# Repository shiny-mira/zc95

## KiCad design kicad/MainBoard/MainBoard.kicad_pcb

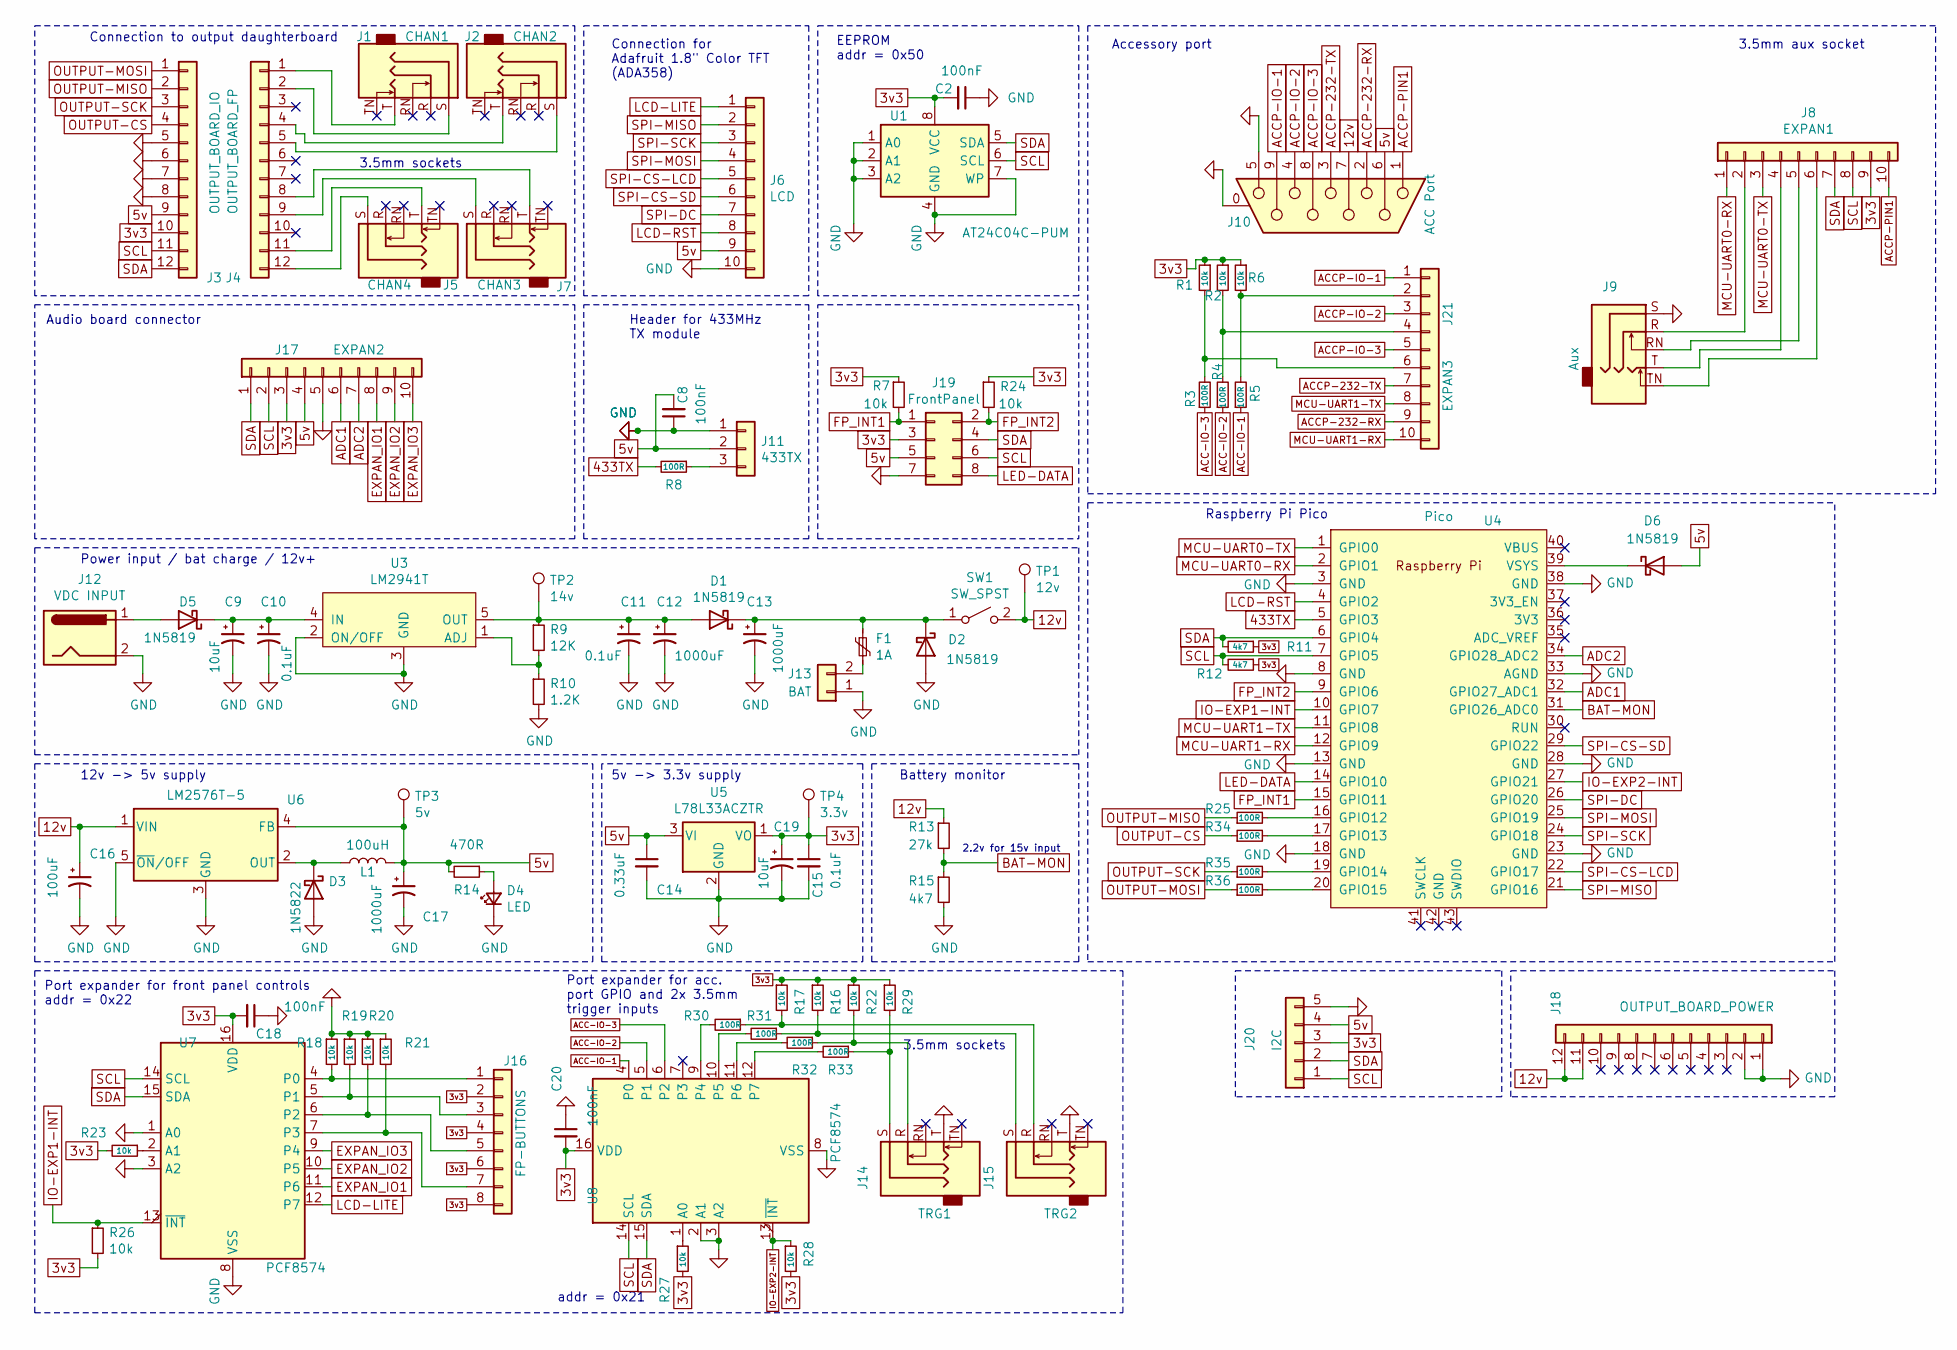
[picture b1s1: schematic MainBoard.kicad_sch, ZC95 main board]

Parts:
C2, C8, C18, C20: 100nF; C_Disc_D3.0mm_W2.0mm_P2.50mm
C9, C19: 10uF; CP_Radial_D5.0mm_P2.00mm
C10, C11, C15: 0.1uF; C_Disc_D3.0mm_W2.0mm_P2.50mm
C12, C13, C17: 1000uF; CP_Radial_D10.0mm_P5.00mm
C14: 0.33uF; C_Disc_D10.5mm_W5.0mm_P5.00mm
C16: 100uF; CP_Radial_D6.3mm_P2.50mm
D1, D2, D5, D6: 1N5819; D_DO-41_SOD81_P10.16mm_Horizontal
D3: 1N5822; D_DO-201AD_P15.24mm_Horizontal
D4: LED; PinSocket_1x02_P2.54mm_Vertical
F1: 1A; Fuse_Littelfuse_395Series
J1: CHAN1; STX31005N
J2: CHAN2; STX31005N
J3: OUTPUT_BOARD_IO; PinSocket_1x12_P2.54mm_Vertical
J4: OUTPUT_BOARD_FP; PinSocket_1x12_P2.54mm_Vertical
J5: CHAN4; STX31005N
J6: LCD; PinSocket_1x10_P2.54mm_Vertical
J7: CHAN3; STX31005N
J8: EXPAN1; PinSocket_1x10_P2.54mm_Vertical
J9: Aux; STX31005N
J10: ACC Port; DSUB-9_Female_Horizontal_P2.77x2.84mm_EdgePinOffset7.70mm_H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
J11: 433TX; PinSocket_1x03_P2.54mm_Vertical
J12: VDC INPUT; DC-005-2.5A-2.0
J13: BAT; Molex_Mini-Fit_Jr_5566-02A_2x01_P4.20mm_Vertical
J14: TRG1; STX31005N
J15: TRG2; STX31005N
J16: FP-BUTTONS; PinSocket_1x08_P2.54mm_Vertical
J17: EXPAN2; PinSocket_1x10_P2.54mm_Vertical
J18: OUTPUT_BOARD_POWER; PinSocket_1x12_P2.54mm_Vertical
J19: FrontPanel; IDC-Header_2x04_P2.54mm_Vertical
J20: I2C; PinSocket_1x05_P2.54mm_Vertical
J21: EXPAN3; PinSocket_1x10_P2.54mm_Vertical
L1: 100uH; L_Radial_D9.5mm_P5.00mm_Fastron_07HVP
R1, R2, R6, R7, R16, R17, R18, R19, R20, R21, R22, R23, R24, R26, R27, R28, R29: 10k; R_Axial_DIN0207_L6.3mm_D2.5mm_P10.16mm_Horizontal
R3, R4, R5, R8, R25, R30, R31, R32, R33, R34, R35, R36: 100R; R_Axial_DIN0207_L6.3mm_D2.5mm_P10.16mm_Horizontal
R9: 12K; R_Axial_DIN0207_L6.3mm_D2.5mm_P10.16mm_Horizontal
R10: 1.2K; R_Axial_DIN0207_L6.3mm_D2.5mm_P10.16mm_Horizontal
R11, R12, R15: 4k7; R_Axial_DIN0207_L6.3mm_D2.5mm_P10.16mm_Horizontal
R13: 27k; R_Axial_DIN0207_L6.3mm_D2.5mm_P10.16mm_Horizontal
R14: 470R; R_Axial_DIN0207_L6.3mm_D2.5mm_P10.16mm_Horizontal
SW1: SW_SPST; SS-12D06L5
TP1: 12v; TestPoint_Pad_1.0x1.0mm
TP2: 14v; TestPoint_Pad_1.0x1.0mm
TP3: 5v; TestPoint_Pad_1.0x1.0mm
TP4: 3.3v; TestPoint_Pad_1.0x1.0mm
U1: AT24C04C-PUM; DIP-8_W7.62mm_Socket
U3: LM2941T; TO-220-5_Horizontal_TabDown
U4: Pico; RPi_Pico_SMD_TH
U5: L78L33ACZTR; TO-92_Inline_Wide
U6: LM2576T-5; TO-220-5_Vertical
U7, U8: PCF8574; DIP-16_W7.62mm_Socket

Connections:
3v3: C2.2, C15.1, C18.2, C19.1, C20.2, J3.10, J8.9, J16.2, J16.4, J16.6, J16.8, J17.3, J19.3, J20.3, R1.1, R2.1, R6.1, R7.1, R11.1, R12.1, R16.1, R17.1, R22.1, R23.2, R24.1, R26.2, R27.2, R28.2, R29.1, TP4.1, U1.8 (VCC), U5.1 (VO), U7.16 (VDD), U8.16 (VDD)
5v: C8.2, C14.1, C17.1, D6.2 (A), J3.9, J6.9, J10.6, J11.2, J17.4, J19.5, J20.4, L1.2, R14.2, TP3.1, U5.3 (VI), U6.4 (FB)
12v: C16.1, J10.7, J18.11, J18.12, R13.1, SW1.2 (B), TP1.1, U6.1 (VIN)
433TX: R8.2, U4.5 (GPIO3)
ACC-IO-1: R5.1, U8.4 (P0)
ACC-IO-2: R4.1, U8.5 (P1)
ACC-IO-3: R3.1, U8.6 (P2)
ACCP-232-RX: J10.2, J21.9
ACCP-232-TX: J10.3, J21.7
ACCP-IO-1: J10.9, J21.1
ACCP-IO-2: J10.4, J21.3
ACCP-IO-3: J10.8, J21.5
ACCP-PIN1: J8.10, J10.1
ADC1: J17.6, U4.32 (GPIO27_ADC1)
ADC2: J17.7, U4.34 (GPIO28_ADC2)
BAT-MON: R13.2, R15.1, U4.31 (GPIO26_ADC0)
EXPAN_IO1: J17.8, U7.11 (P6)
EXPAN_IO2: J17.9, U7.10 (P5)
EXPAN_IO3: J17.10, U7.9 (P4)
FP_INT1: J19.1, R7.2, U4.15 (GPIO11)
FP_INT2: J19.2, R24.2, U4.9 (GPIO6)
GND: C2.1, C8.1, C9.2, C10.2, C11.2, C12.2, C13.2, C14.2, C15.2, C16.2, C17.2, C18.1, C19.2, C20.1, D2.2 (A), D3.2 (A), D4.1 (K), J3.5, J3.6, J3.7, J3.8, J6.10, J9.S, J10.0 (PAD), J10.5, J11.1, J12.2, J13.1, J14.T, J15.T, J17.5, J18.1, J18.2, J19.7, J20.5, R10.2, R15.2, R18.1, R19.1, R20.1, R21.1, U1.1 (A0), U1.2 (A1), U1.3 (A2), U1.4 (GND), U1.7 (WP), U3.2 (ON/OFF), U3.3 (GND), U4.3 (GND), U4.8 (GND), U4.13 (GND), U4.18 (GND), U4.23 (GND), U4.28 (GND), U4.33 (AGND), U4.38 (GND), U5.2 (GND), U6.3 (GND), U6.5 (~ON/OFF), U7.1 (A0), U7.3 (A2), U7.8 (VSS), U8.2 (A1), U8.3 (A2), U8.8 (VSS)
IO-EXP1-INT: R26.1, U4.10 (GPIO7), U7.13 (~INT)
IO-EXP2-INT: R28.1, U4.27 (GPIO21), U8.13 (~INT)
LCD-LITE: J6.1, U7.12 (P7)
LCD-RST: J6.8, U4.4 (GPIO2)
LED-DATA: J19.8, U4.14 (GPIO10)
MCU-UART0-RX: J8.1, U4.2 (GPIO1)
MCU-UART0-TX: J8.3, U4.1 (GPIO0)
MCU-UART1-RX: J21.10, U4.12 (GPIO9)
MCU-UART1-TX: J21.8, U4.11 (GPIO8)
unnamed: C11.1, C12.1, D1.2 (A), R9.1, TP2.1, U3.5 (OUT)
unnamed: C13.1, D1.1 (K), D2.1 (K), F1.1, SW1.1 (A)
unnamed: D3.1 (K), L1.1, U6.2 (OUT)
unnamed: D4.2 (A), R14.1
unnamed: D5.2 (A), J12.1
unnamed: C9.1, C10.1, D5.1 (K), U3.4 (IN)
unnamed: D6.1 (K), U4.39 (VSYS)
unnamed: J1.T, J4.1
unnamed: J1.S, J4.2
unnamed: J2.T, J4.4
unnamed: J2.S, J4.5
unnamed: J4.8, J7.T
unnamed: J4.9, J7.S
unnamed: J4.11, J5.T
unnamed: J4.12, J5.S
unnamed: J8.2, J9.R
unnamed: J8.4, J9.T
unnamed: J8.5, J9.RN
unnamed: J8.6, J9.TN
unnamed: J11.3, R8.1
unnamed: F1.2, J13.2
unnamed: J14.R, R22.2, R32.1
unnamed: J14.S, R29.2, R33.1
unnamed: J15.R, R17.2, R30.1
unnamed: J15.S, R16.2, R31.1
unnamed: J16.1, R18.2, U7.4 (P0)
unnamed: J16.3, R19.2, U7.5 (P1)
unnamed: J16.5, R20.2, U7.6 (P2)
unnamed: J16.7, R21.2, U7.7 (P3)
unnamed: J21.2, R5.2, R6.2
unnamed: J21.4, R2.2, R4.2
unnamed: J21.6, R1.2, R3.2
unnamed: R9.2, R10.1, U3.1 (ADJ)
unnamed: R25.2, U4.16 (GPIO12)
unnamed: R34.2, U4.17 (GPIO13)
unnamed: R35.2, U4.19 (GPIO14)
unnamed: R36.2, U4.20 (GPIO15)
unnamed: R23.1, U7.2 (A1)
unnamed: R27.1, U8.1 (A0)
unnamed: R30.2, U8.9 (P4)
unnamed: R31.2, U8.10 (P5)
unnamed: R32.2, U8.11 (P6)
unnamed: R33.2, U8.12 (P7)
OUTPUT-CS: J3.4, R34.1
OUTPUT-MISO: J3.2, R25.1
OUTPUT-MOSI: J3.1, R36.1
OUTPUT-SCK: J3.3, R35.1
SCL: J3.11, J8.8, J17.2, J19.6, J20.1, R12.2, U1.6 (SCL), U4.7 (GPIO5), U7.14 (SCL), U8.14 (SCL)
SDA: J3.12, J8.7, J17.1, J19.4, J20.2, R11.2, U1.5 (SDA), U4.6 (GPIO4), U7.15 (SDA), U8.15 (SDA)
SPI-CS-LCD: J6.5, U4.22 (GPIO17)
SPI-CS-SD: J6.6, U4.29 (GPIO22)
SPI-DC: J6.7, U4.26 (GPIO20)
SPI-MISO: J6.2, U4.21 (GPIO16)
SPI-MOSI: J6.4, U4.25 (GPIO19)
SPI-SCK: J6.3, U4.24 (GPIO18)

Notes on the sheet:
3.5mm sockets
Raspberry Pi Pico
Connection to output daughterboard
2.2v for 15v input
addr = 0x21
EEPROM addr = 0x50
3.5mm aux socket
Connection for Adafruit 1.8" Color TFT (ADA358)
Audio board connector
Accessory port
Port expander for acc. port GPIO and 2x 3.5mm trigger inputs
Port expander for front panel controls addr = 0x22
Header for 433MHz TX module
12v -> 5v supply
Battery monitor
Power input / bat charge / 12v+
5v -> 3.3v supply

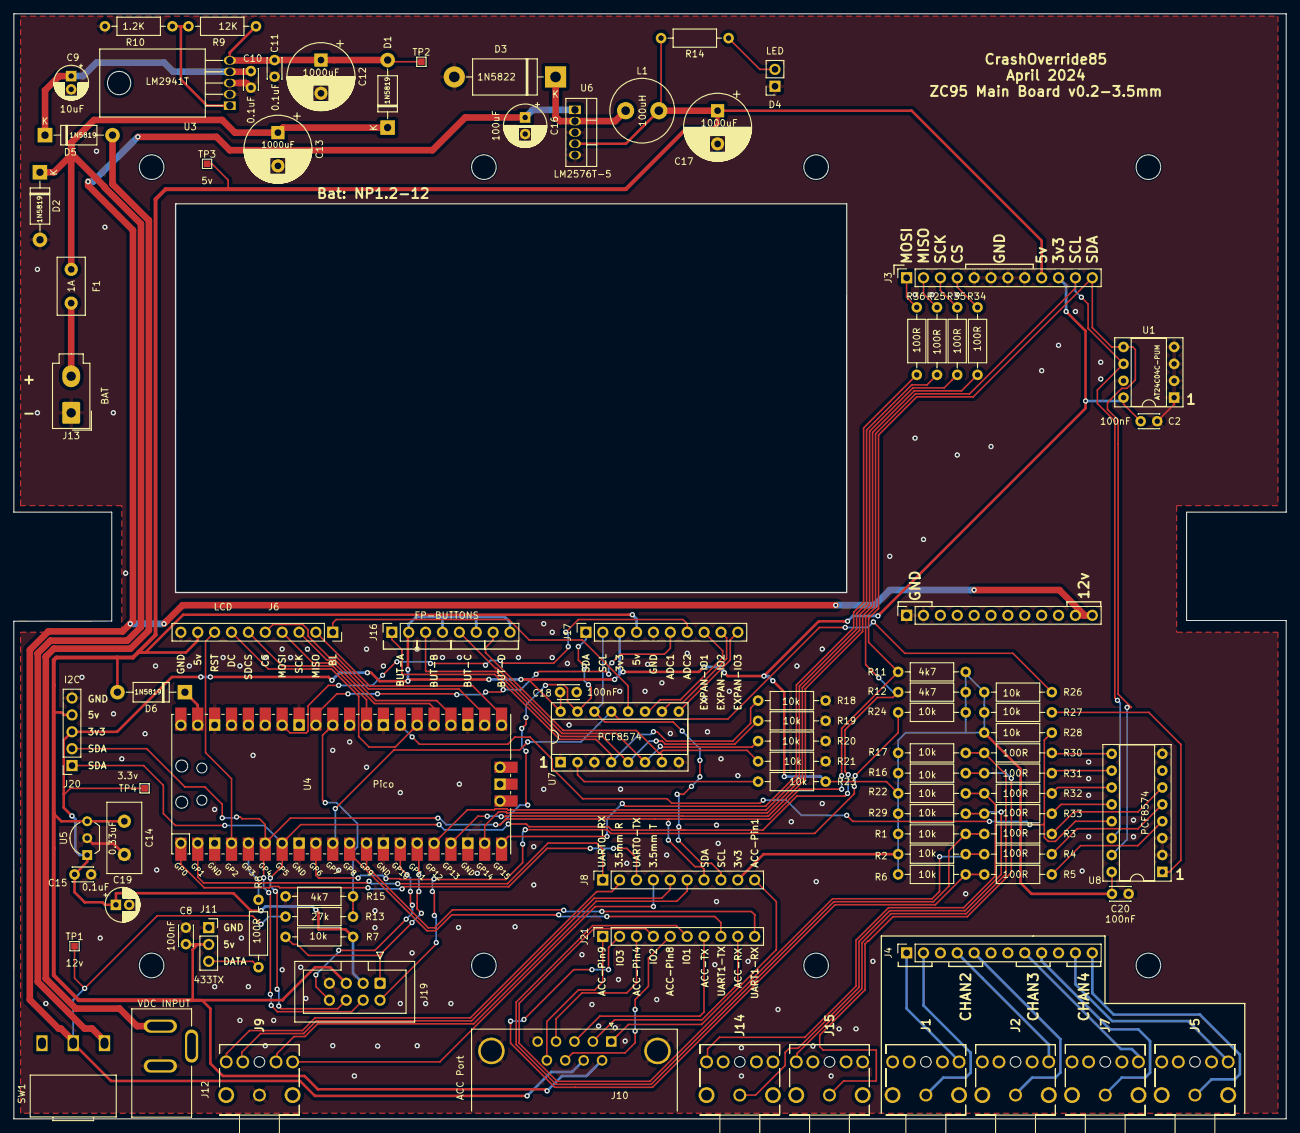
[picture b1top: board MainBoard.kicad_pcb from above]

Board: 2 copper layers, 191.4 x 166.2 mm, 91 parts (0 on the bottom side), 86 nets.

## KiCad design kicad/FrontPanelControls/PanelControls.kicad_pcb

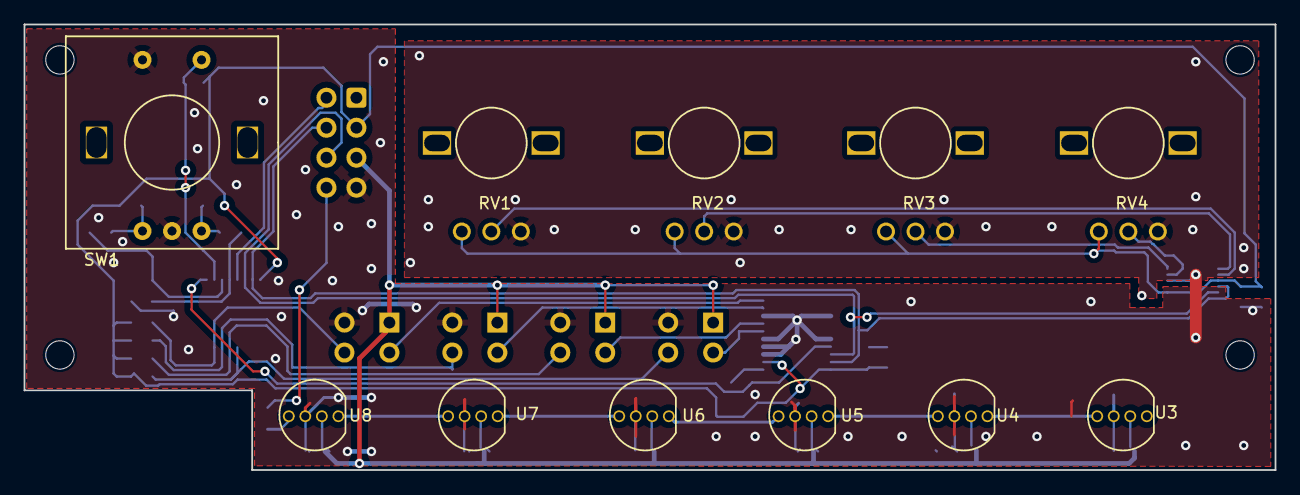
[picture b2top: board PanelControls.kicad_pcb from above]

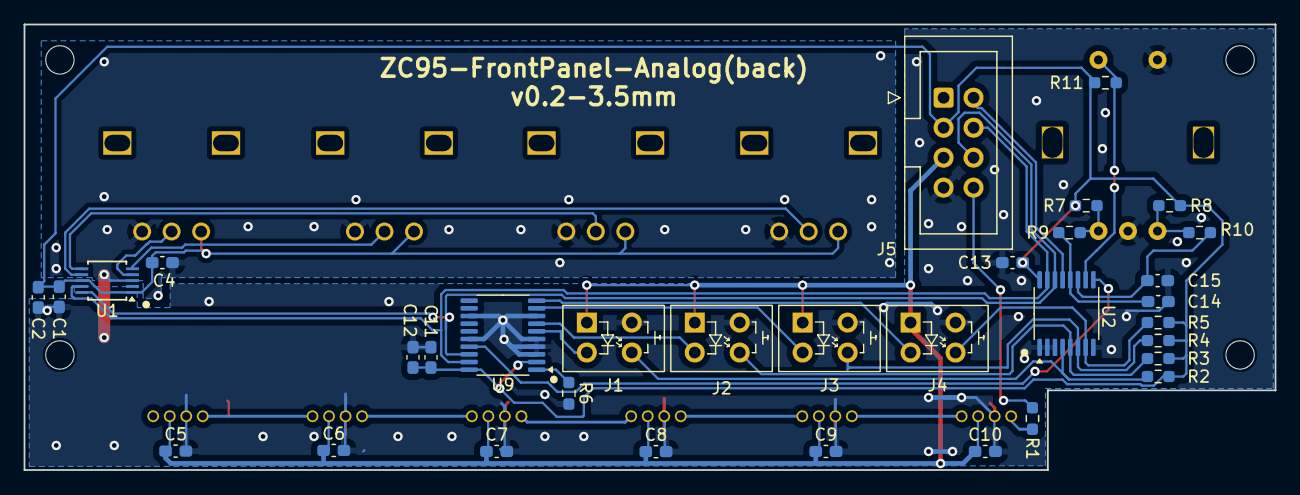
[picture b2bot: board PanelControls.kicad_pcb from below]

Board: 2 copper layers, 106.0 x 37.8 mm, 44 parts (33 on the bottom side), 32 nets.

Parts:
C1, C4, C5, C6, C7, C8, C9, C10, C11, C13, C14, C15: 100nF; C_0603_1608Metric_Pad1.08x0.95mm_HandSolder
C2, C12: 10uF; C_0603_1608Metric_Pad1.08x0.95mm_HandSolder
J1: BUTTON_A; ButtonConnector
J2: BUTTON_B; ButtonConnector
J3: BUTTON_C; ButtonConnector
J4: BUTTON_D; ButtonConnector
J5: Conn_02x04_Odd_Even; IDC-Header_2x04_P2.54mm_Vertical
R1: 100R; R_0603_1608Metric_Pad0.98x0.95mm_HandSolder
R2, R3, R4, R5, R7, R8, R9, R10, R11: 10K; R_0603_1608Metric_Pad0.98x0.95mm_HandSolder
R6: 1K; R_0603_1608Metric_Pad0.98x0.95mm_HandSolder
RV1, RV2, RV3, RV4: R_POT; ALPSALPINE RK09L1140A2U
SW1: ADJ; BOURNS PEC11L-4125F-S0020
U1: ADS1115IDGS; TSSOP-10_3x3mm_P0.5mm
U2: TCA9534; TSSOP-16_4.4x5mm_P0.65mm
U3, U4, U5, U6, U7, U8: WS2812D; WS2812D-F5
U9: TLC59108IPWR; TSSOP-20_4.4x6.5mm_P0.65mm

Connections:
+3v3: C1.1, C2.1, C4.1, C11.1, C12.1, C13.2, J5.3, R2.1, R3.1, R4.1, R5.1, R7.1, R8.1, R11.1, RV1.1, RV2.1, RV3.1, RV4.1, U1.1 (ADDR), U1.8 (VDD), U2.16 (VDD), U9.2 (A0), U9.20 (VCC)
+5v: C5.1, C6.1, C7.1, C8.1, C9.1, C10.1, J1.1, J2.1, J3.1, J4.1, J5.5, U3.2 (VCC), U4.2 (VCC), U5.2 (VCC), U6.2 (VCC), U7.2 (VCC), U8.2 (VCC)
GND: C1.2, C2.2, C4.2, C5.2, C6.2, C7.2, C8.2, C9.2, C10.2, C11.2, C12.2, C13.1, C14.2, C15.2, J1.2, J2.2, J3.2, J4.2, J5.7, R6.2, RV1.3, RV2.3, RV3.3, RV4.3, SW1.C, SW1.S1, U1.3 (GND), U2.1 (A0), U2.2 (A1), U2.3 (A2), U2.8 (GND), U3.3 (GND), U4.3 (GND), U5.3 (GND), U6.3 (GND), U7.3 (GND), U8.3 (GND), U9.3 (A1), U9.4 (A2), U9.5 (A3), U9.8 (GND), U9.13 (GND), U9.16 (GND)
INT2: J5.2, U2.13 (~INT)
LED_DATA: J5.8, R1.1
unnamed: J1.3, U9.6 (~OUT0)
unnamed: J1.4, R2.2, U2.4 (P0)
unnamed: J2.3, U9.7 (~OUT1)
unnamed: J2.4, R3.2, U2.5 (P1)
unnamed: J3.3, U9.9 (~OUT2)
unnamed: J3.4, R4.2, U2.6 (P2)
unnamed: J4.3, U9.10 (~OUT3)
unnamed: J4.4, R5.2, U2.7 (P3)
unnamed: R1.2, U8.4 (DIN)
unnamed: R6.1, U9.1 (REXT)
unnamed: R7.2, R9.2, SW1.B
unnamed: R8.2, R10.1, SW1.A
unnamed: RV1.2, U1.7 (AIN3)
unnamed: RV2.2, U1.6 (AIN2)
unnamed: RV3.2, U1.5 (AIN1)
unnamed: RV4.2, U1.4 (AIN0)
unnamed: U3.4 (DIN), U4.1 (DOUT)
unnamed: U4.4 (DIN), U5.1 (DOUT)
unnamed: U5.4 (DIN), U6.1 (DOUT)
unnamed: U6.4 (DIN), U7.1 (DOUT)
unnamed: U7.4 (DIN), U8.1 (DOUT)
RESET: U2.9 (P4), U9.17 (~RESET)
ROT5-A: C15.1, R10.2, U2.11 (P6)
ROT5-B: C14.1, R9.1, U2.12 (P7)
ROT5-BUT: R11.2, SW1.S2, U2.10 (P5)
SCL: J5.6, U1.10 (SCL), U2.14 (SCL), U9.18 (SCL)
SDA: J5.4, U1.9 (SDA), U2.15 (SDA), U9.19 (SDA)

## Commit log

2024-03-27 Remove unnecessary files
2024-03-27 Convert schematic to KiCad 8
2024-03-27 Convert board to Kicad 8
2024-03-27 Switch Mainboard Q1, D1, D2, D5 with 1N5819
2024-03-27 Fix outline
2024-03-27 Move things a bit for potential additional header
2024-03-27 Add header for RS232 configuration
2024-03-27 Before 3.5mm footprint switch
2024-03-28 Switch everything to 3.5mm plugs
2024-04-05 One more 3d model
2024-04-05 No more 12v rs232 - move to UART
2024-04-07 Small changes to expander
2024-04-08 More tiny mainboard updates
2024-04-08 fix edge cut violations on front panel
2024-04-08 Rename FrontPanel
2024-04-08 FrontPanel MainBoard alignment
2024-04-08 3d models for Panel Controls
2024-04-08 Move to fit new 3.5mm holes
2024-04-22 Fix missing connection on mainboard
2024-04-22 Add optional design for a Back panel
2024-11-02 Fix connections of output jacks
